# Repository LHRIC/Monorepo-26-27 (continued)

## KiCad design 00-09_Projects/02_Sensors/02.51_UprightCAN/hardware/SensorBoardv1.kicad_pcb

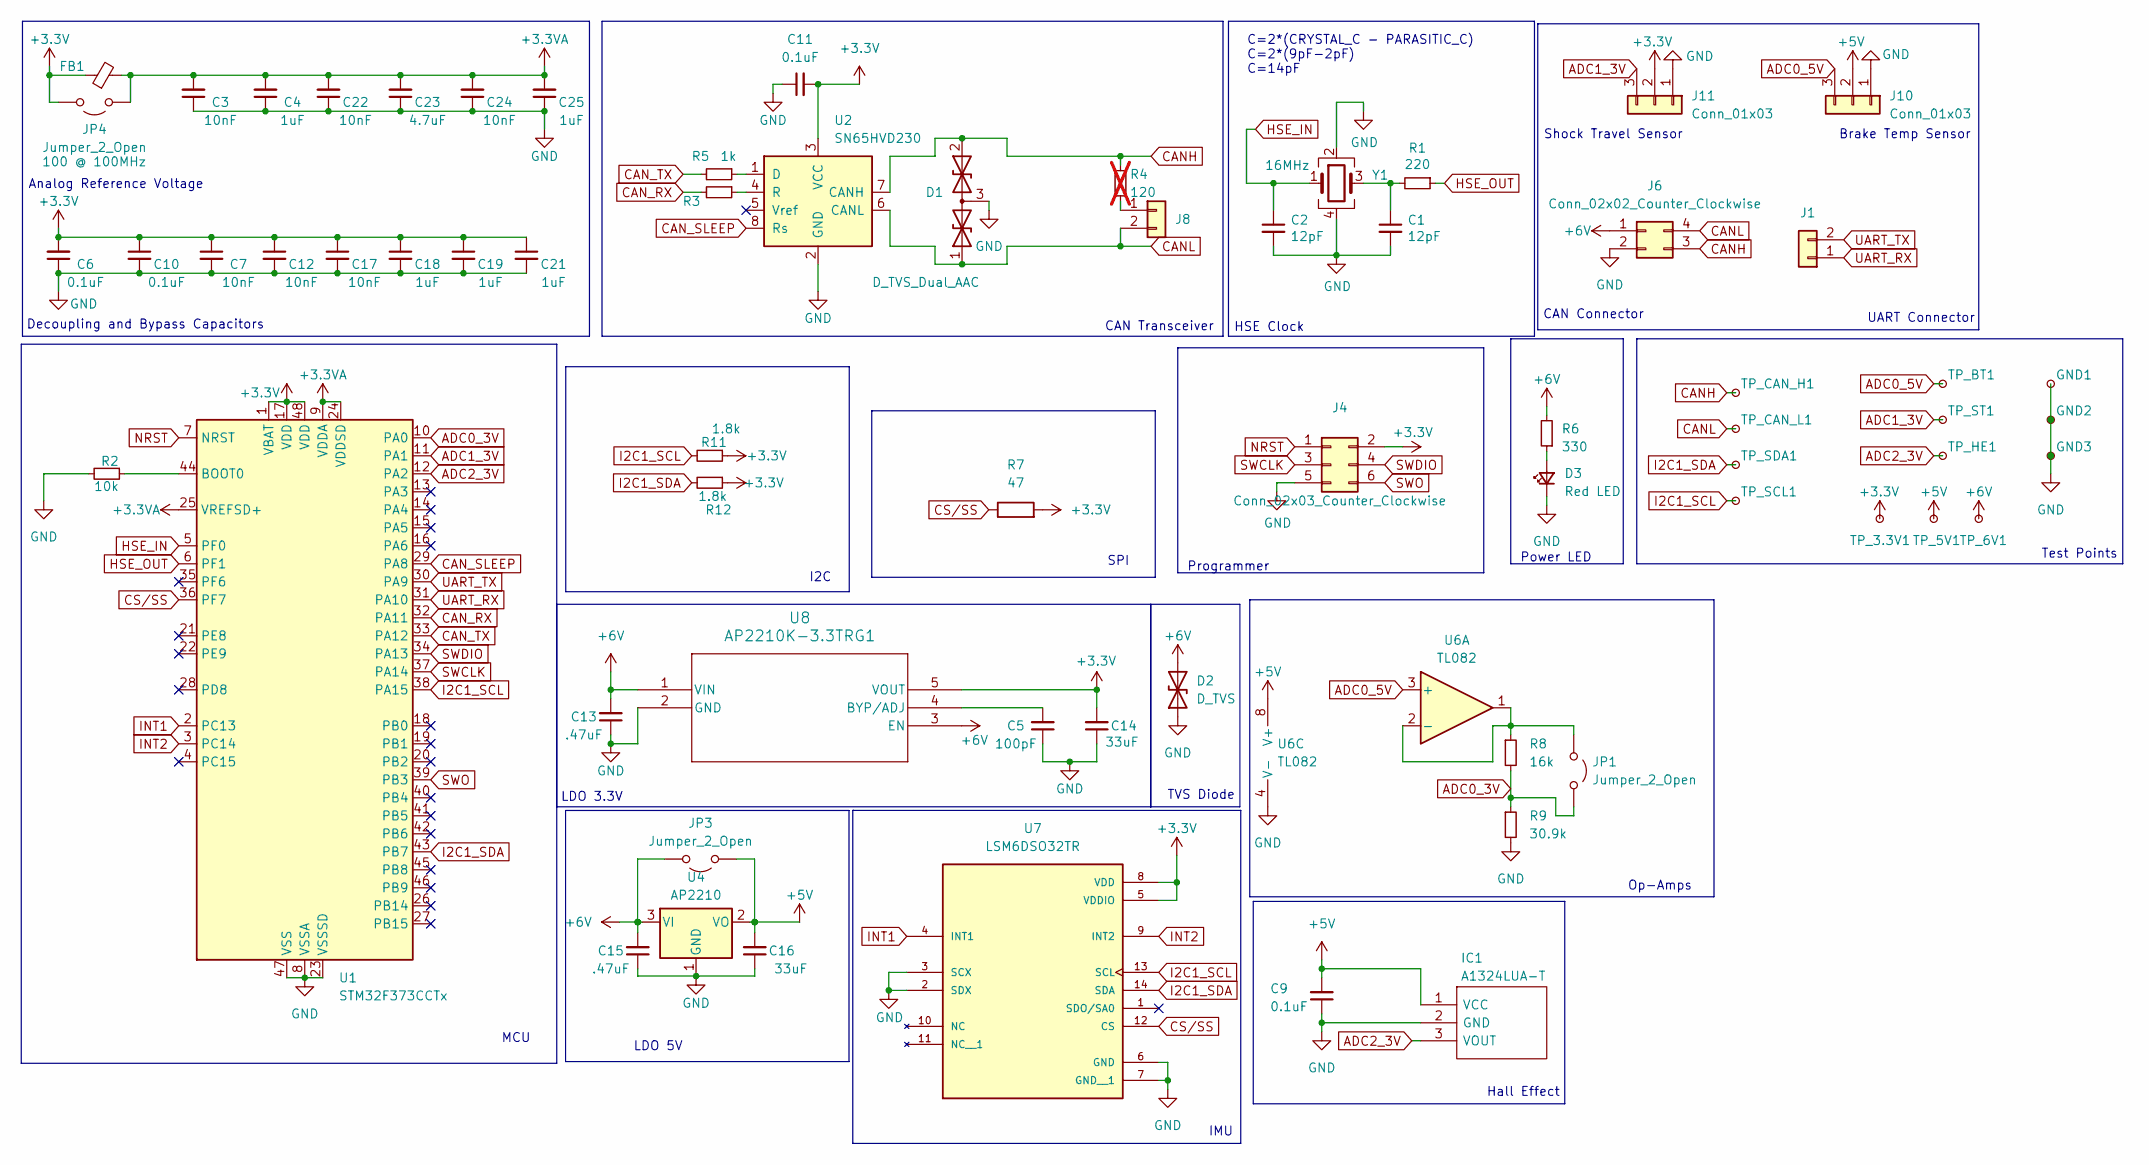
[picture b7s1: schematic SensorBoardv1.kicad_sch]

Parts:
C1, C2: 12pF; C_0402_1005Metric
C3, C7, C12, C17, C22, C24: 10nF; C_0603_1608Metric
C4, C18, C19, C21, C25: 1uF; C_0603_1608Metric
C5: 100pF; C_0603_1608Metric
C6, C9, C10, C11: 0.1uF; C_0603_1608Metric
C13, C15: .47uF; C_0603_1608Metric
C14, C16: 33uF; C_0805_2012Metric
C23: 4.7uF; C_0603_1608Metric
D1: D_TVS_Dual_AAC; SOT-23-3
D2: D_TVS; D_SMB
D3: Red LED; LED_0603_1608Metric
FB1: 100 @ 100MHz; R_0402_1005Metric
GND1, GND2, GND3: TestPoint_Pad_D2.0mm
IC1: A1324LUA-T; A1157LUAT; Mouser Part Number 250-A1324LUA-T
J1, J8: Conn_01x02; PinHeader_1x02_P2.54mm_Vertical
J4: Conn_02x03_Counter_Clockwise; Molex_Micro-Fit_3.0_43045-0612_2x03_P3.00mm_Vertical
J6: Conn_02x02_Counter_Clockwise; Molex_Micro-Fit_3.0_43045-0400_2x02_P3.00mm_Horizontal
J10, J11: Conn_01x03; Molex_Micro-Fit_3.0_43650-0315_1x03_P3.00mm_Vertical
JP1, JP3, JP4: Jumper_2_Open; SolderJumper-2_P1.3mm_Open_RoundedPad1.0x1.5mm
R1: 220; R_0603_1608Metric
R2: 10k; R_0603_1608Metric
R3, R5: 1k; R_0603_1608Metric
R4: 120; R_0603_1608Metric; not fitted
R6: 330; R_0603_1608Metric
R7: 47; R_0603_1608Metric
R8: 16k; R_0603_1608Metric
R9: 30.9k; R_0603_1608Metric
R11, R12: 1.8k; R_0603_1608Metric
TP_3.3V1, TP_5V1, TP_6V1: TestPoint_Pad_D2.0mm
TP_BT1: TestPoint_Pad_D2.0mm
TP_CAN_H1: TestPoint_Pad_D2.0mm
TP_CAN_L1: CAN_L; TestPoint_Pad_D2.0mm
TP_HE1: TestPoint_Pad_D2.0mm
TP_SCL1: CAN_L; TestPoint_Pad_D2.0mm
TP_SDA1: TestPoint_Pad_D2.0mm
TP_ST1: TestPoint_Pad_D2.0mm
U1: STM32F373CCTx; LQFP-48_7x7mm_P0.5mm
U2: SN65HVD230; SOIC-8_3.9x4.9mm_P1.27mm
U4: AP2210; SOT-23-3
U6: TL082; D8
U7: LSM6DSO32TR; XDCR_LSM6DSO32TR; PARTREV 1
U8: AP2210K-3.3TRG1; SOT-23-5_DIO
Y1: 16MHz; Crystal_SMD_3225-4Pin_3.2x2.5mm

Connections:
+3.3V: C6.2, C7.1, C10.1, C11.2, C12.1, C14.2, C17.1, C18.1, C19.1, C21.1, FB1.1, J4.2, J11.2, JP4.2 (B), R7.2, R11.1, R12.1, TP_3.3V1.1, U1.1 (VBAT), U1.17 (VDD), U1.48 (VDD), U2.3 (VCC), U7.5 (VDDIO), U7.8 (VDD), U8.5 (VOUT)
+3.3VA: C3.2, C4.2, C22.2, C23.2, C24.2, C25.2, FB1.2, JP4.1 (A), U1.9 (VDDA), U1.24 (VDDSD), U1.25 (VREFSD+)
+5V: C9.2, C16.2, IC1.1 (VCC), J10.2, JP3.1 (A), TP_5V1.1, U4.2 (VO), U6.8 (V+)
+6V: C13.2, C15.2, D2.2 (A2), J6.1, JP3.2 (B), R6.2, TP_6V1.1, U4.3 (VI), U8.1 (VIN), U8.3 (EN)
ADC0_3V: JP1.2 (B), R8.2, R9.1, U1.10 (PA0)
ADC0_5V: J10.3, TP_BT1.1, U6.3 (+)
ADC1_3V: J11.3, TP_ST1.1, U1.11 (PA1)
ADC2_3V: IC1.3 (VOUT), TP_HE1.1, U1.12 (PA2)
CANH: D1.2 (A2), J6.3, R4.2, TP_CAN_H1.1, U2.7 (CANH)
CANL: D1.1 (A1), J6.4, J8.2, TP_CAN_L1.1, U2.6 (CANL)
CAN_RX: R3.2, U1.32 (PA11)
CAN_SLEEP: U1.29 (PA8), U2.8 (Rs)
CAN_TX: R5.2, U1.33 (PA12)
CS/SS: R7.1, U1.36 (PF7), U7.12 (CS)
GND: C1.2, C2.2, C3.1, C4.1, C5.1, C6.1, C7.2, C9.1, C10.2, C11.1, C12.2, C13.1, C14.1, C15.1, C16.1, C17.2, C18.2, C19.2, C21.2, C22.1, C23.1, C24.1, C25.1, D1.3 (common), D2.1 (A1), D3.1 (K), GND1.1, GND2.1, GND3.1, IC1.2 (GND), J4.5, J6.2, J10.1, J11.1, R2.2, R9.2, U1.8 (VSSA), U1.23 (VSSSD), U1.47 (VSS), U2.2 (GND), U4.1 (GND), U6.4 (V-), U7.2 (SDX), U7.3 (SCX), U7.6 (GND), U7.7 (GND__1), U8.2 (GND), Y1.2, Y1.4
HSE_IN: C2.1, U1.5 (PF0), Y1.1
HSE_OUT: R1.1, U1.6 (PF1)
I2C1_SCL: R11.2, TP_SCL1.1, U1.38 (PA15), U7.13 (SCL)
I2C1_SDA: R12.2, TP_SDA1.1, U1.43 (PB7), U7.14 (SDA)
INT1: U1.2 (PC13), U7.4 (INT1)
INT2: U1.3 (PC14), U7.9 (INT2)
NRST: J4.1, U1.7 (NRST)
unnamed: C1.1, R1.2, Y1.3
unnamed: D3.2 (A), R6.1
unnamed: J8.1, R4.1
unnamed: JP1.1 (A), R8.1, U6.1, U6.2 (-)
unnamed: R2.1, U1.44 (BOOT0)
unnamed: R5.1, U2.1 (D)
unnamed: R3.1, U2.4 (R)
unnamed: C5.2, U8.4 (BYP/ADJ)
SWCLK: J4.3, U1.37 (PA14)
SWDIO: J4.4, U1.34 (PA13)
SWO: J4.6, U1.39 (PB3)
UART_RX: J1.1, U1.31 (PA10)
UART_TX: J1.2, U1.30 (PA9)

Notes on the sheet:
Op-Amps
CAN Connector
Decoupling and Bypass Capacitors
Shock Travel Sensor
IMU
Test Points
C=2*(CRYSTAL_C - PARASITIC_C) C=2*(9pF-2pF) C=14pF
UART Connector
CAN Transceiver
MCU
HSE Clock
TVS Diode
SPI
Power LED
Hall Effect
LDO 3.3V
Programmer
Analog Reference Voltage
Brake Temp Sensor
LDO 5V
I2C

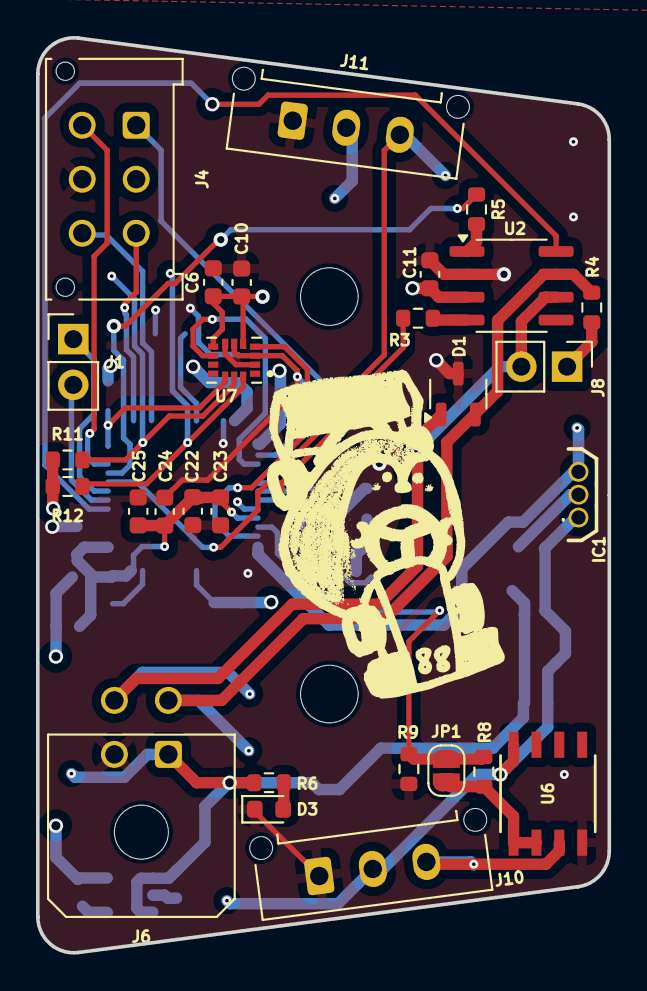
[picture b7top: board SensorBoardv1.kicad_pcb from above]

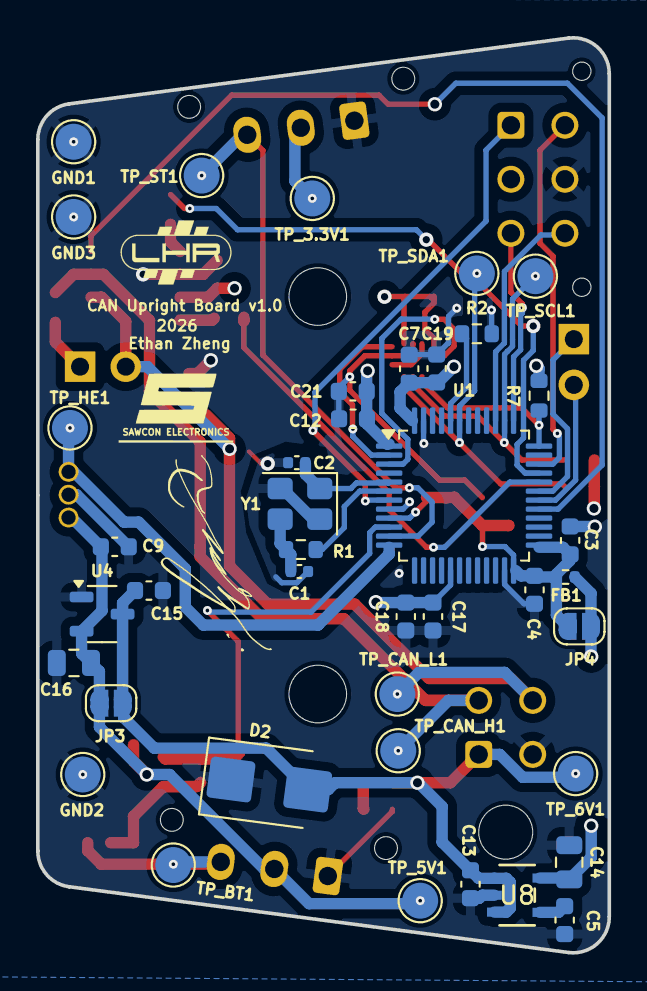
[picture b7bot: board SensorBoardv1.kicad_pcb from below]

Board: 4 copper layers, 31.8 x 50.8 mm, 71 parts (41 on the bottom side), 35 nets.

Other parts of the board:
H1, H2: MountingHole; MountingHole_3.2mm_M3
Sig_S: LOGO; Signature_Small

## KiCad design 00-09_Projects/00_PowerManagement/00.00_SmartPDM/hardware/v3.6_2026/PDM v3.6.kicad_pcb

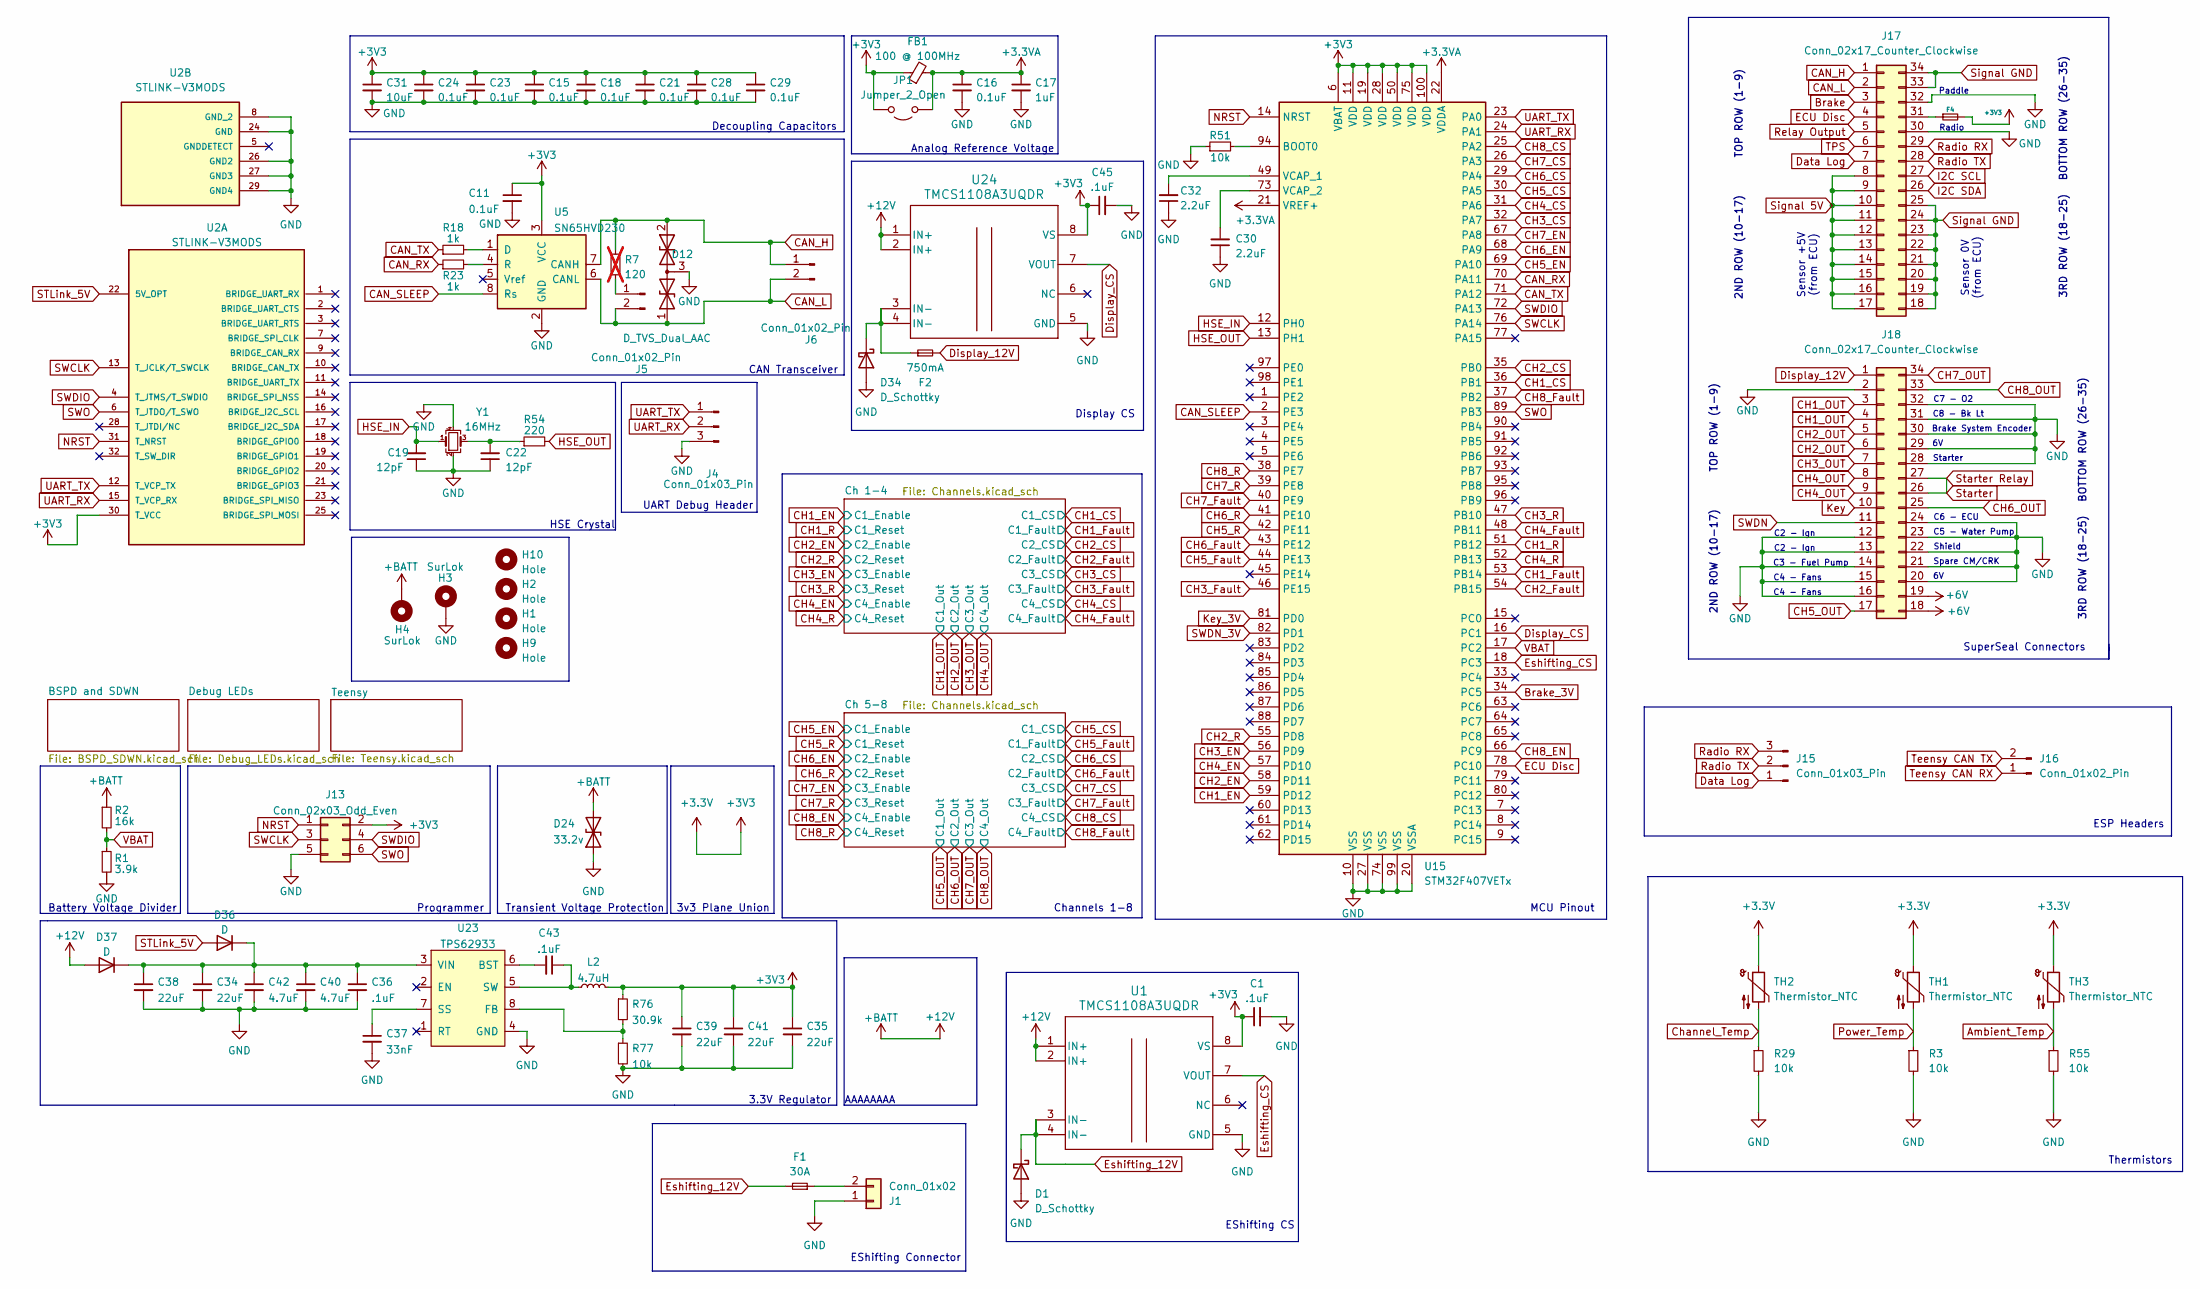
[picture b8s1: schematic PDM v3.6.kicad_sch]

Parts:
C1, C36, C43, C45: .1uF; C_0603_1608Metric
C11, C15, C16, C18, C21, C23, C24, C28, C29: 0.1uF; C_0603_1608Metric
C17: 1uF; C_0603_1608Metric
C19, C22: 12pF; C_0402_1005Metric
C30, C32: 2.2uF; C_0603_1608Metric
C31: 10uF; C_0805_2012Metric
C34, C35, C38, C39, C41: 22uF; C_0805_2012Metric
C37: 33nF; C_0603_1608Metric
C40, C42: 4.7uF; C_0805_2012Metric
D1, D34: D_Schottky; D_SOD-523
D12: D_TVS_Dual_AAC; SOT-23
D24: 33.2v; D_SMB
D36, D37: D; D_PowerDI-123
F1: 30A; 806Series_Fuse
F2: 750mA; Fuse_1206_3216Metric
F4: Fuse_1206_3216Metric; LCSC C70071
FB1: 100 @ 100MHz; C_0402_1005Metric
H1, H2, H9, H10: Hole; MountingHole_3.2mm_M3
H3, H4: SurLok; SurLok_5.7
J1: Conn_01x02; AMASS_XT30U-F_1x02_P5.0mm_Vertical
J4, J15: Conn_01x03_Pin; PinHeader_1x03_P2.54mm_Vertical
J5, J6, J16: Conn_01x02_Pin; PinHeader_1x02_P2.54mm_Vertical
J13: Conn_02x03_Odd_Even; Molex_Micro-Fit_3.0_43045-0612_2x03_P3.00mm_Vertical
J17: Conn_02x17_Counter_Clockwise; TE_6437288-1
J18: Conn_02x17_Counter_Clockwise; TE_6437288-2
JP1: Jumper_2_Open; SolderJumper-2_P1.3mm_Open_RoundedPad1.0x1.5mm
L2: 4.7uH; SRU8043-4R7Y
R1: 3.9k; R_0603_1608Metric
R2: 16k; R_0603_1608Metric
R3, R29, R51, R55, R77: 10k; R_0603_1608Metric
R7: 120; R_0603_1608Metric; not fitted
R18, R23: 1k; R_0603_1608Metric
R54: 220; R_0603_1608Metric
R76: 30.9k; R_0603_1608Metric
TH1, TH2, TH3: Thermistor_NTC; R_0402_1005Metric
U1, U24: TMCS1108A3UQDR; SOIC-8_3.9x4.9mm_P1.27mm
U2: STLINK-V3MODS; MODULE_STLINK-V3MODS; PARTREV 1; DigiKey_Part_Number 497-STLINK-V3MODS-ND
U5: SN65HVD230; SOIC-8_3.9x4.9mm_P1.27mm
U15: STM32F407VETx; LQFP-100_14x14mm_P0.5mm
U23: TPS62933; SOT-583
Y1: 16MHz; Crystal_SMD_3225-4Pin_3.2x2.5mm

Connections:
+3.3V: C1.1, C11.1, C15.1, C18.1, C21.1, C23.1, C24.1, C28.1, C29.1, C31.1, C35.1, C39.1, C41.1, C45.1, F4.2, FB1.1, J13.2, JP1.2 (B), L2.2, R76.1, TH1.1, TH2.1, TH3.1, U1.8 (VS), U2.30 (T_VCC), U5.3 (VCC), U15.6 (VBAT), U15.11 (VDD), U15.19 (VDD), U15.28 (VDD), U15.50 (VDD), U15.75 (VDD), U15.100 (VDD), U24.8 (VS); also elsewhere on the board
+3.3VA: C16.1, C17.1, FB1.2, JP1.1 (A), U15.21 (VREF+), U15.22 (VDDA)
+6V: J18.18, J18.19; also elsewhere on the board
+12V: D24.2 (A2), D37.2 (A), H4.1, R2.1, U1.1 (IN+), U1.2 (IN+), U24.1 (IN+), U24.2 (IN+); also elsewhere on the board
Ambient_Temp: R55.1, TH3.2; also elsewhere on the board
Brake: J17.3; also elsewhere on the board
Brake_3V: U15.34 (PC5); also elsewhere on the board
CAN_H: D12.2 (A2), J6.1, J17.1, R7.1, U5.7 (CANH); also elsewhere on the board
CAN_L: D12.1 (A1), J5.2, J6.2, J17.2, U5.6 (CANL); also elsewhere on the board
CAN_RX: R23.1, U15.70 (PA11)
CAN_SLEEP: U5.8 (Rs), U15.2 (PE3)
CAN_TX: R18.1, U15.71 (PA12)
CH1_CS: U15.36 (PB1); also elsewhere on the board
CH1_EN: U15.59 (PD12); also elsewhere on the board
CH1_Fault: U15.53 (PB14); also elsewhere on the board
CH1_OUT: J18.3, J18.4; also elsewhere on the board
CH1_R: U15.51 (PB12); also elsewhere on the board
CH2_CS: U15.35 (PB0); also elsewhere on the board
CH2_EN: U15.58 (PD11); also elsewhere on the board
CH2_Fault: U15.54 (PB15); also elsewhere on the board
CH2_OUT: J18.5, J18.6; also elsewhere on the board
CH2_R: U15.55 (PD8); also elsewhere on the board
CH3_CS: U15.32 (PA7); also elsewhere on the board
CH3_EN: U15.56 (PD9); also elsewhere on the board
CH3_Fault: U15.46 (PE15); also elsewhere on the board
CH3_OUT: J18.7; also elsewhere on the board
CH3_R: U15.47 (PB10); also elsewhere on the board
CH4_CS: U15.31 (PA6); also elsewhere on the board
CH4_EN: U15.57 (PD10); also elsewhere on the board
CH4_Fault: U15.48 (PB11); also elsewhere on the board
CH4_OUT: J18.8, J18.9; also elsewhere on the board
CH4_R: U15.52 (PB13); also elsewhere on the board
CH5_CS: U15.30 (PA5); also elsewhere on the board
CH5_EN: U15.69 (PA10); also elsewhere on the board
CH5_Fault: U15.44 (PE13); also elsewhere on the board
CH5_OUT: J18.17; also elsewhere on the board
CH5_R: U15.42 (PE11); also elsewhere on the board
CH6_CS: U15.29 (PA4); also elsewhere on the board
CH6_EN: U15.68 (PA9); also elsewhere on the board
CH6_Fault: U15.43 (PE12); also elsewhere on the board
CH6_OUT: J18.25; also elsewhere on the board
CH6_R: U15.41 (PE10); also elsewhere on the board
CH7_CS: U15.26 (PA3); also elsewhere on the board
CH7_EN: U15.67 (PA8); also elsewhere on the board
CH7_Fault: U15.40 (PE9); also elsewhere on the board
CH7_OUT: J18.34; also elsewhere on the board
CH7_R: U15.39 (PE8); also elsewhere on the board
CH8_CS: U15.25 (PA2); also elsewhere on the board
CH8_EN: U15.66 (PC9); also elsewhere on the board
CH8_Fault: U15.37 (PB2); also elsewhere on the board
CH8_OUT: J18.33; also elsewhere on the board
CH8_R: U15.38 (PE7); also elsewhere on the board
Channel_Temp: R29.1, TH2.2; also elsewhere on the board
Data Log: J15.1, J17.7; also elsewhere on the board
Display_12V: F2.2, J18.1
Display_CS: U15.16 (PC1), U24.7 (VOUT)
ECU Disc: J17.4, U15.78 (PC10); also elsewhere on the board
Eshifting_12V: D1.1 (K), F1.2, U1.3 (IN-), U1.4 (IN-)
Eshifting_CS: U1.7 (VOUT), U15.18 (PC3)
GND: C1.2, C11.2, C15.2, C16.2, C17.2, C18.2, C19.1, C21.2, C22.1, C23.2, C24.2, C28.2, C29.2, C30.1, C31.2, C32.1, C34.2, C35.2, C36.2, C37.2, C38.2, C39.2, C40.2, C41.2, C42.2, C45.2, D1.2 (A), D12.3 (common), D24.1 (A1), D34.2 (A), H3.1, J1.1, J4.3, J13.5, J17.30, J17.32, J18.2, J18.12, J18.13, J18.14, J18.15, J18.16, J18.20, J18.21, J18.22, J18.23, J18.24, J18.28, J18.29, J18.30, J18.31, J18.32, R1.2, R3.2, R29.2, R51.1, R55.2, R77.2, U1.5 (GND), U2.8 (GND_2), U2.24 (GND), U2.26 (GND2), U2.27 (GND3), U2.29 (GND4), U5.2 (GND), U15.10 (VSS), U15.20 (VSSA), U15.27 (VSS), U15.74 (VSS), U15.99 (VSS), U23.4 (GND), U24.5 (GND), Y1.2, Y1.4; also elsewhere on the board
HSE_IN: C19.2, U15.12 (PH0), Y1.1
HSE_OUT: R54.2, U15.13 (PH1)
I2C SCL: J17.27; also elsewhere on the board
I2C SDA: J17.26; also elsewhere on the board
Key: J18.10; also elsewhere on the board
Key_3V: U15.81 (PD0); also elsewhere on the board
NRST: J13.1, U2.31 (T_NRST), U15.14 (NRST)
unnamed: C22.2, R54.1, Y1.3
unnamed: D34.1 (K), F2.1, U24.3 (IN-), U24.4 (IN-)
unnamed: C34.1, C36.1, C38.1, C40.1, C42.1, D36.1 (K), D37.1 (K), U23.3 (VIN)
unnamed: F1.1, J1.2
unnamed: J5.1, R7.2
unnamed: F4.1, J17.31
unnamed: R18.2, U5.1 (D)
unnamed: R23.2, U5.4 (R)
unnamed: R51.2, U15.94 (BOOT0)
unnamed: C32.2, U15.49 (VCAP_1)
unnamed: C30.2, U15.73 (VCAP_2)
unnamed: C43.2, U23.6 (BST)
unnamed: R76.2, R77.1, U23.8 (FB)
unnamed: C37.1, U23.7 (SS)
unnamed: C43.1, L2.1, U23.5 (SW)
Power_Temp: R3.1, TH1.2; also elsewhere on the board
Radio RX: J15.3, J17.29; also elsewhere on the board
Radio TX: J15.2, J17.28; also elsewhere on the board
Relay Output: J17.5; also elsewhere on the board
STLink_5V: D36.2 (A), U2.22 (5V_OPT)
SWCLK: J13.3, U2.13 (T_JCLK/T_SWCLK), U15.76 (PA14)
SWDIO: J13.4, U2.4 (T_JTMS/T_SWDIO), U15.72 (PA13)
SWDN: J18.11; also elsewhere on the board
SWDN_3V: U15.82 (PD1); also elsewhere on the board
SWO: J13.6, U2.6 (T_JTDO/T_SWO), U15.89 (PB3)
Signal 5V: J17.8, J17.9, J17.10, J17.11, J17.12, J17.13, J17.14, J17.15, J17.16, J17.17
Signal GND: J17.18, J17.19, J17.20, J17.21, J17.22, J17.23, J17.24, J17.25, J17.33, J17.34
Starter: J18.26, J18.27
TPS: J17.6; also elsewhere on the board
Teensy CAN RX: J16.1; also elsewhere on the board
Teensy CAN TX: J16.2; also elsewhere on the board
UART_RX: J4.2, U2.15 (T_VCP_RX), U15.24 (PA1)
UART_TX: J4.1, U2.12 (T_VCP_TX), U15.23 (PA0)
VBAT: R1.1, R2.2, U15.17 (PC2)

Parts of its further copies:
C26: 0.1uF; C_0603_1608Metric

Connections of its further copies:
+3.3V: C26.1; also elsewhere on the board
GND: C26.2; also elsewhere on the board

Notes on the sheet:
MCU Pinout
Radio
EShifting Connector
2ND ROW (10-17)
EShifting CS
C4 - Fans
C2 - Ign
AAAAAAAA
TOP ROW (1-9)
3v3 Plane Union
3RD ROW (18-25)
C8 - Bk Lt
Starter
Shield
C3 - Fuel Pump
C5 - Water Pump
Transient Voltage Protection
UART Debug Header
Sensor +5V (from ECU)
Thermistors
CAN Transceiver
BOTTOM ROW (26-35)
Battery Voltage Divider
Brake System Encoder
HSE Crystal
SuperSeal Connectors
C6 - ECU
Paddle
Decoupling Capacitors
Display CS
ESP Headers
Channels 1-8
3.3V Regulator
Programmer
C7 - O2
Analog Reference Voltage
Sensor 0V (from ECU)
Spare CM/CRK

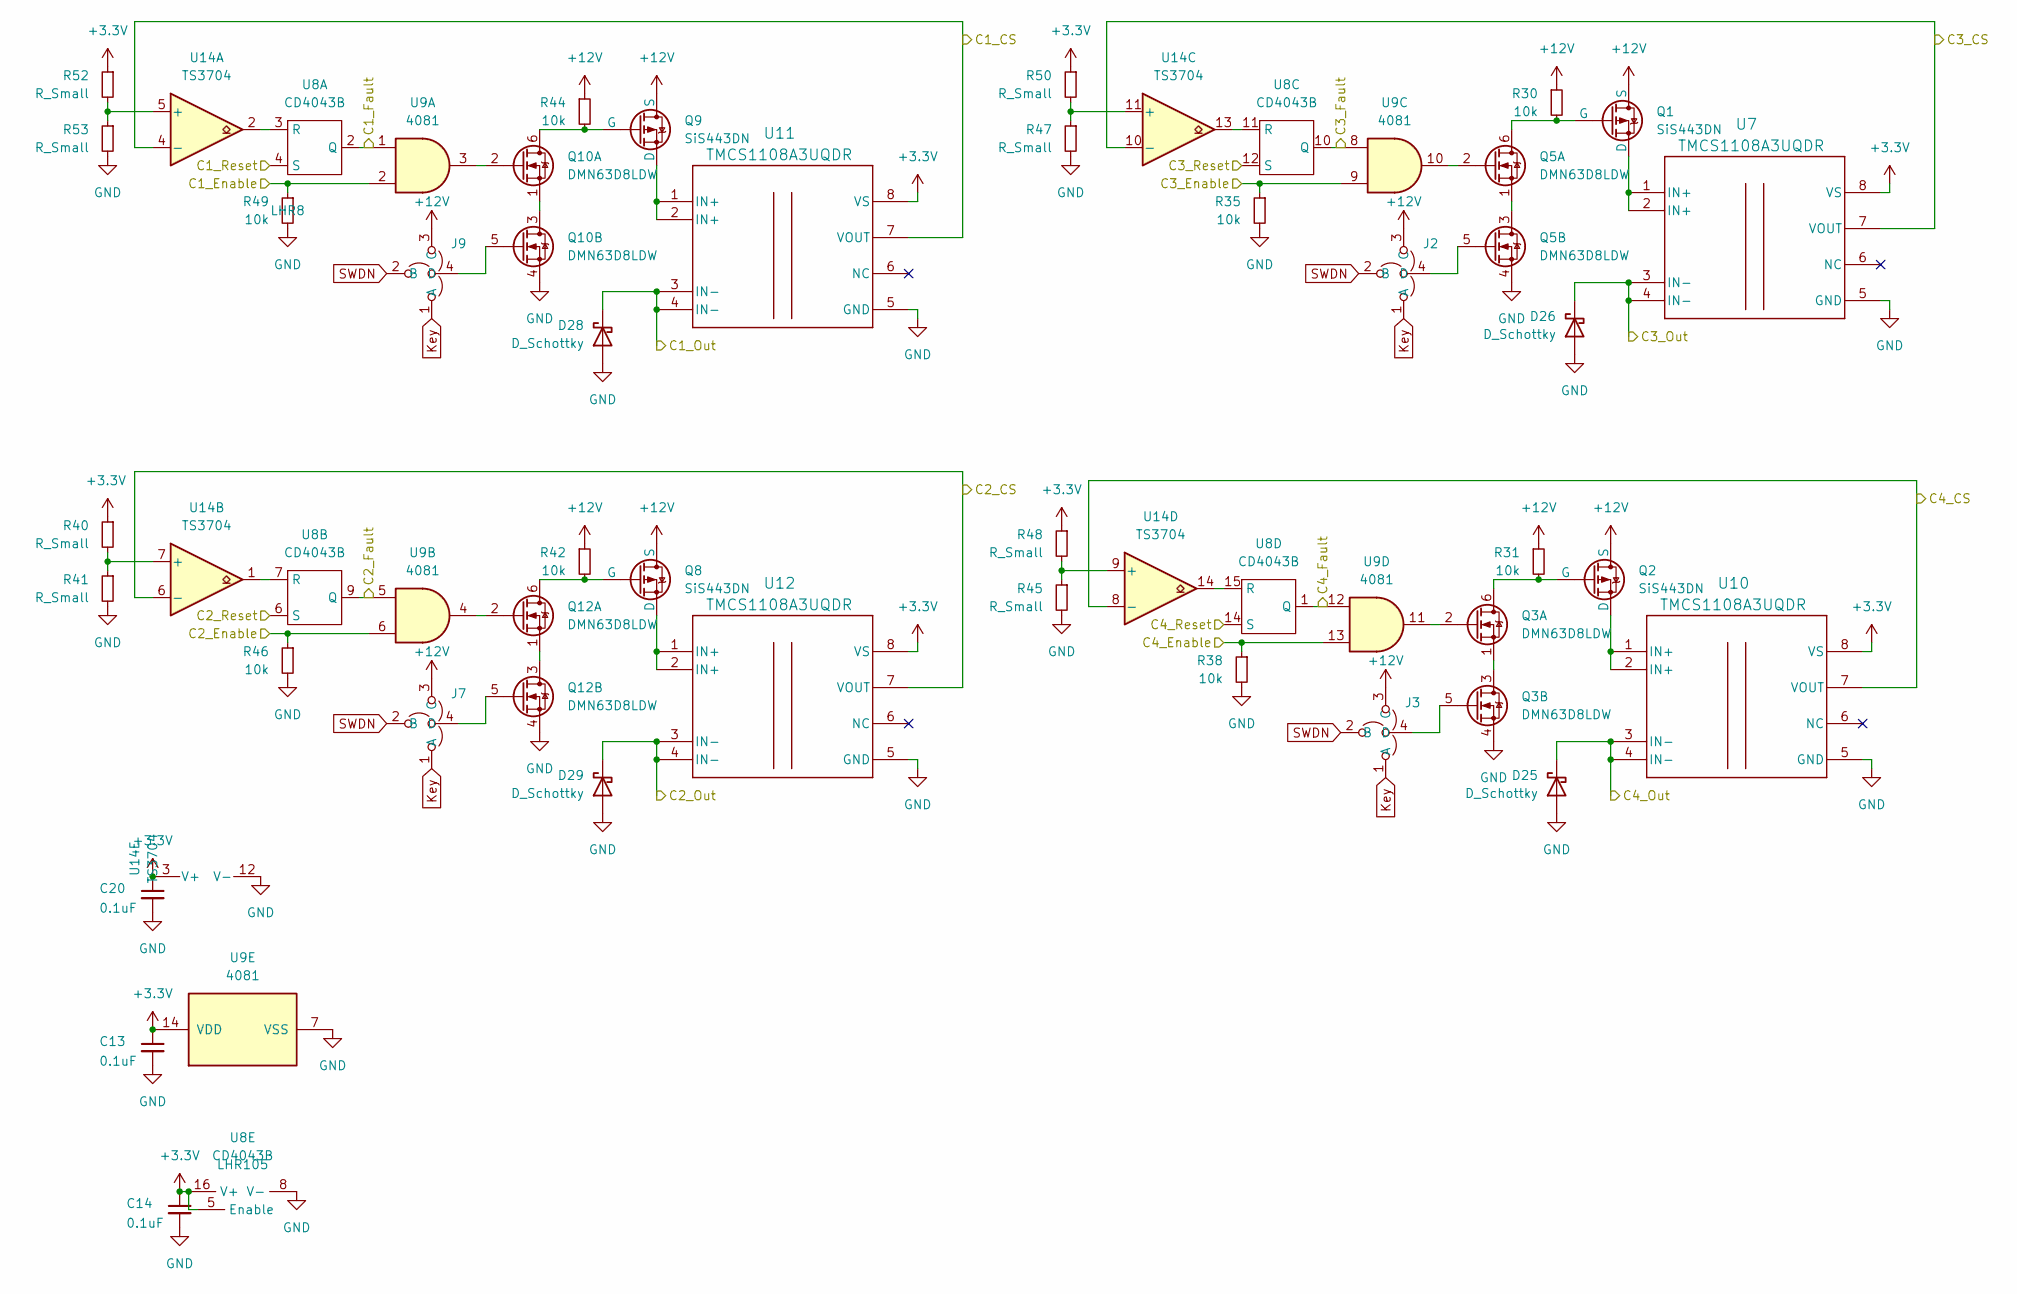
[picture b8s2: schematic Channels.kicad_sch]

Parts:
C13, C14, C20: 0.1uF; C_0603_1608Metric
D25, D26, D28, D29: D_Schottky; D_SOD-523
J2, J3, J7, J9: SolderJumper-4_P1.3mm_Open_Rounded
Q1, Q2, Q8, Q9: SiS443DN; Vishay_PowerPAK_1212-8_Single
Q3, Q5, Q10, Q12: DMN63D8LDW; SOT-363_SC-70-6
R30, R31, R35, R38, R42, R44, R46, R49: 10k; R_0603_1608Metric
R40, R41, R45, R47, R48, R50, R52, R53: R_Small; R_0603_1608Metric
U7, U10, U11, U12: TMCS1108A3UQDR; SOIC-8_3.9x4.9mm_P1.27mm
U8: CD4043B; SOIC-16_3.9x9.9mm_P1.27mm
U9: 4081; TSSOP-14_4.4x5mm_P0.65mm
U14: TS3704; TSSOP-14_4.4x5mm_P0.65mm

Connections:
+3.3V: C13.1, C14.1, C20.1, R40.1, R48.1, R50.1, R52.1, U7.8 (VS), U8.5 (Enable), U8.16 (V+), U9.14 (VDD), U10.8 (VS), U11.8 (VS), U12.8 (VS), U14.3 (V+); also elsewhere on the board
+12V: J2.3 (C), J3.3 (C), J7.3 (C), J9.3 (C), Q1.1 (S), Q1.2 (S), Q1.3 (S), Q2.1 (S), Q2.2 (S), Q2.3 (S), Q8.1 (S), Q8.2 (S), Q8.3 (S), Q9.1 (S), Q9.2 (S), Q9.3 (S), R30.1, R31.1, R42.1, R44.1; also elsewhere on the board
CH5_CS: U11.7 (VOUT), U14.4 (-); also elsewhere on the board
CH5_EN: R49.1, U9.2; also elsewhere on the board
CH5_Fault: U8.2 (Q), U9.1; also elsewhere on the board
CH5_OUT: D28.1 (K), U11.3 (IN-), U11.4 (IN-); also elsewhere on the board
CH5_R: U8.4 (S); also elsewhere on the board
CH6_CS: U12.7 (VOUT), U14.6 (-); also elsewhere on the board
CH6_EN: R46.1, U9.6; also elsewhere on the board
CH6_Fault: U8.9 (Q), U9.5; also elsewhere on the board
CH6_OUT: D29.1 (K), U12.3 (IN-), U12.4 (IN-); also elsewhere on the board
CH6_R: U8.6 (S); also elsewhere on the board
CH7_CS: U7.7 (VOUT), U14.10 (-); also elsewhere on the board
CH7_EN: R35.1, U9.9; also elsewhere on the board
CH7_Fault: U8.10 (Q), U9.8; also elsewhere on the board
CH7_OUT: D26.1 (K), U7.3 (IN-), U7.4 (IN-); also elsewhere on the board
CH7_R: U8.12 (S); also elsewhere on the board
CH8_CS: U10.7 (VOUT), U14.8 (-); also elsewhere on the board
CH8_EN: R38.1, U9.13; also elsewhere on the board
CH8_Fault: U8.1 (Q), U9.12; also elsewhere on the board
CH8_OUT: D25.1 (K), U10.3 (IN-), U10.4 (IN-); also elsewhere on the board
CH8_R: U8.14 (S); also elsewhere on the board
GND: C13.2, C14.2, C20.2, D25.2 (A), D26.2 (A), D28.2 (A), D29.2 (A), Q3.4 (S), Q5.4 (S), Q10.4 (S), Q12.4 (S), R35.2, R38.2, R41.2, R45.2, R46.2, R47.2, R49.2, R53.2, U7.5 (GND), U8.8 (V-), U9.7 (VSS), U10.5 (GND), U11.5 (GND), U12.5 (GND), U14.12 (V-); also elsewhere on the board
Key: J2.1 (A), J3.1 (A), J7.1 (A), J9.1 (A); also elsewhere on the board
unnamed: J2.4 (D), Q5.5 (G)
unnamed: J3.4 (D), Q3.5 (G)
unnamed: J7.4 (D), Q12.5 (G)
unnamed: J9.4 (D), Q10.5 (G)
unnamed: Q1.5 (D), U7.1 (IN+), U7.2 (IN+)
unnamed: Q1.4 (G), Q5.6 (D), R30.2
unnamed: Q2.5 (D), U10.1 (IN+), U10.2 (IN+)
unnamed: Q2.4 (G), Q3.6 (D), R31.2
unnamed: Q3.2 (G), U9.11
unnamed: Q3.1 (S), Q3.3 (D)
unnamed: Q5.2 (G), U9.10
unnamed: Q5.1 (S), Q5.3 (D)
unnamed: Q8.5 (D), U12.1 (IN+), U12.2 (IN+)
unnamed: Q9.5 (D), U11.1 (IN+), U11.2 (IN+)
unnamed: Q9.4 (G), Q10.6 (D), R44.2
unnamed: Q10.2 (G), U9.3
unnamed: Q10.1 (S), Q10.3 (D)
unnamed: Q8.4 (G), Q12.6 (D), R42.2
unnamed: Q12.2 (G), U9.4
unnamed: Q12.1 (S), Q12.3 (D)
unnamed: U8.3 (R), U14.2
unnamed: U8.7 (R), U14.1
unnamed: U8.11 (R), U14.13
unnamed: U8.15 (R), U14.14
unnamed: R52.2, R53.1, U14.5 (+)
unnamed: R40.2, R41.1, U14.7 (+)
unnamed: R47.1, R50.2, U14.11 (+)
unnamed: R45.1, R48.2, U14.9 (+)
SWDN: J2.2 (B), J3.2 (B), J7.2 (B), J9.2 (B); also elsewhere on the board

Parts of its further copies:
C25, C26, C27: 0.1uF; C_0603_1608Metric
D27, D30, D31, D32: D_Schottky; D_SOD-523
J8, J10, J11, J12: SolderJumper-4_P1.3mm_Open_Rounded
Q7, Q13, Q14, Q15: SiS443DN; Vishay_PowerPAK_1212-8_Single
Q11, Q16, Q17, Q18: DMN63D8LDW; SOT-363_SC-70-6
R43, R56, R57, R58, R66, R67, R70, R71: 10k; R_0603_1608Metric
R59, R60, R61, R62, R63, R64, R65, R68: R_Small; R_0603_1608Metric
U13, U16, U19, U20: TMCS1108A3UQDR; SOIC-8_3.9x4.9mm_P1.27mm
U17: CD4043B; SOIC-16_3.9x9.9mm_P1.27mm
U18: TS3704; TSSOP-14_4.4x5mm_P0.65mm
U21: 4081; TSSOP-14_4.4x5mm_P0.65mm

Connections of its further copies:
+3.3V: C25.1, C26.1, C27.1, R63.1, R64.1, R65.1, R68.1, U13.8 (VS), U16.8 (VS), U17.5 (Enable), U17.16 (V+), U18.3 (V+), U19.8 (VS), U20.8 (VS), U21.14 (VDD); also elsewhere on the board
+12V: J8.3 (C), J10.3 (C), J11.3 (C), J12.3 (C), Q7.1 (S), Q7.2 (S), Q7.3 (S), Q13.1 (S), Q13.2 (S), Q13.3 (S), Q14.1 (S), Q14.2 (S), Q14.3 (S), Q15.1 (S), Q15.2 (S), Q15.3 (S), R43.1, R56.1, R57.1, R58.1; also elsewhere on the board
CH1_CS: U18.4 (-), U20.7 (VOUT); also elsewhere on the board
CH1_EN: R66.1, U21.2; also elsewhere on the board
CH1_Fault: U17.2 (Q), U21.1; also elsewhere on the board
CH1_OUT: D32.1 (K), U20.3 (IN-), U20.4 (IN-); also elsewhere on the board
CH1_R: U17.4 (S); also elsewhere on the board
CH2_CS: U16.7 (VOUT), U18.6 (-); also elsewhere on the board
CH2_EN: R67.1, U21.6; also elsewhere on the board
CH2_Fault: U17.9 (Q), U21.5; also elsewhere on the board
CH2_OUT: D31.1 (K), U16.3 (IN-), U16.4 (IN-); also elsewhere on the board
CH2_R: U17.6 (S); also elsewhere on the board
CH3_CS: U18.10 (-), U19.7 (VOUT); also elsewhere on the board
CH3_EN: R70.1, U21.9; also elsewhere on the board
CH3_Fault: U17.10 (Q), U21.8; also elsewhere on the board
CH3_OUT: D30.1 (K), U19.3 (IN-), U19.4 (IN-); also elsewhere on the board
CH3_R: U17.12 (S); also elsewhere on the board
CH4_CS: U13.7 (VOUT), U18.8 (-); also elsewhere on the board
CH4_EN: R71.1, U21.13; also elsewhere on the board
CH4_Fault: U17.1 (Q), U21.12; also elsewhere on the board
CH4_OUT: D27.1 (K), U13.3 (IN-), U13.4 (IN-); also elsewhere on the board
CH4_R: U17.14 (S); also elsewhere on the board
GND: C25.2, C26.2, C27.2, D27.2 (A), D30.2 (A), D31.2 (A), D32.2 (A), Q11.4 (S), Q16.4 (S), Q17.4 (S), Q18.4 (S), R59.2, R60.2, R61.2, R62.2, R66.2, R67.2, R70.2, R71.2, U13.5 (GND), U16.5 (GND), U17.8 (V-), U18.12 (V-), U19.5 (GND), U20.5 (GND), U21.7 (VSS); also elsewhere on the board
Key: J8.1 (A), J10.1 (A), J11.1 (A), J12.1 (A); also elsewhere on the board
unnamed: J8.4 (D), Q11.5 (G)
unnamed: J10.4 (D), Q18.5 (G)
unnamed: J11.4 (D), Q17.5 (G)
unnamed: J12.4 (D), Q16.5 (G)
unnamed: Q7.5 (D), U13.1 (IN+), U13.2 (IN+)
unnamed: Q7.4 (G), Q11.6 (D), R43.2
unnamed: Q11.2 (G), U21.11
unnamed: Q11.1 (S), Q11.3 (D)
unnamed: Q13.5 (D), U19.1 (IN+), U19.2 (IN+)
unnamed: Q13.4 (G), Q16.6 (D), R57.2
unnamed: Q14.5 (D), U20.1 (IN+), U20.2 (IN+)
unnamed: Q14.4 (G), Q18.6 (D), R58.2
unnamed: Q15.5 (D), U16.1 (IN+), U16.2 (IN+)
unnamed: Q15.4 (G), Q17.6 (D), R56.2
unnamed: Q16.2 (G), U21.10
unnamed: Q16.1 (S), Q16.3 (D)
unnamed: Q17.2 (G), U21.4
unnamed: Q17.1 (S), Q17.3 (D)
unnamed: Q18.2 (G), U21.3
unnamed: Q18.1 (S), Q18.3 (D)
unnamed: U17.3 (R), U18.2
unnamed: U17.7 (R), U18.1
unnamed: U17.11 (R), U18.13
unnamed: U17.15 (R), U18.14
unnamed: R61.1, R68.2, U18.5 (+)
unnamed: R59.1, R64.2, U18.7 (+)
unnamed: R62.1, R63.2, U18.11 (+)
unnamed: R60.1, R65.2, U18.9 (+)
SWDN: J8.2 (B), J10.2 (B), J11.2 (B), J12.2 (B); also elsewhere on the board
